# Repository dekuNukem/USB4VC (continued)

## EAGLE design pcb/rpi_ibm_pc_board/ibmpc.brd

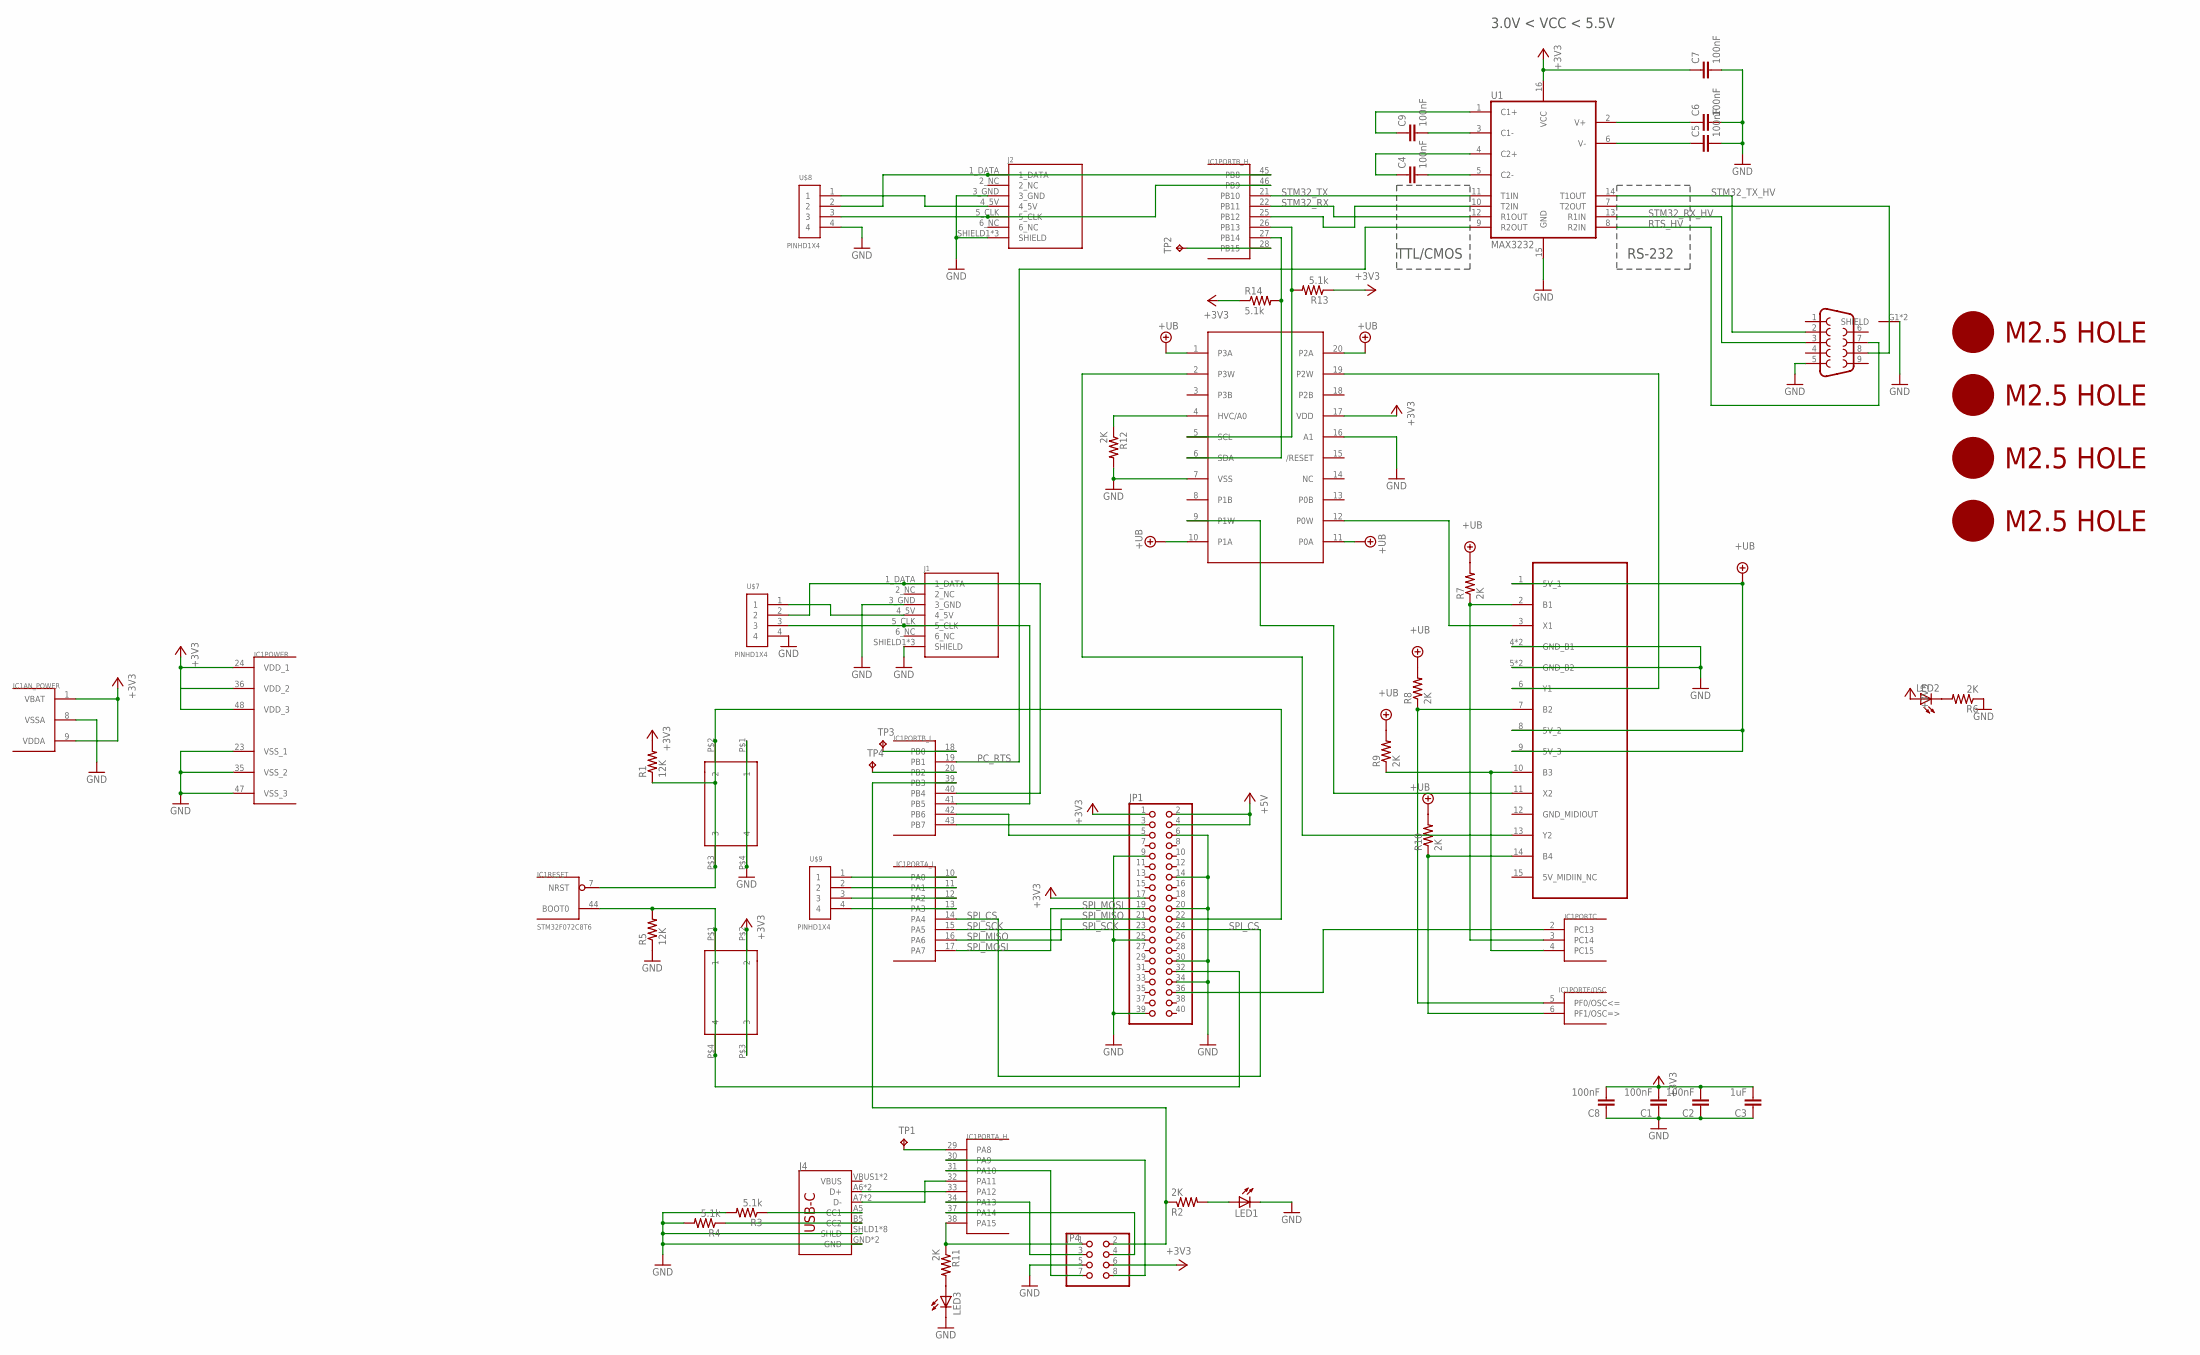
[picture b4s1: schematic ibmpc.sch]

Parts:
C1, C2, C4, C5, C6, C7, C8, C9: 100nF; 0805@1
C3: 1uF; 0805@1
IC1: STM32F072C8T6; TQFP48
J1, J2: DIN7
J3: DB9MALE; DB9_MALE
J4: USB_C16PIN; USB-C-16P
JP1: PINHD-2X20-BIG; 2X20-BIG
JP4: PINHD-2X4; 2X04
LED1, LED2, LED3: LEDCHIP-LED0805; CHIP-LED0805
R1, R5: 12K; 0805
R2, R6, R7, R8, R9, R10, R11, R12: 2K; 0805
R3, R4, R13, R14: 5.1k; 0805
SW1, SW4: 324_SW; 342_SWICH_FOOT
TP1, TP2, TP3, TP4: TPTP12R; TP12R
U1: MAX3232; SO016
U$1: GAMEPORT_15P; DA15
U$2, U$3, U$4, U$5: M2.5HOLE
U$6: MCP4451; TSSOP20
U$7, U$8, U$9: PINHD1X4; 1X04-CLEANBIG

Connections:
+3V3: C1.2, C2.2, C3.2, C7.1, C8.2, IC1.1 (VBAT), IC1.9 (VDDA), IC1.24 (VDD_1), IC1.36 (VDD_2), IC1.48 (VDD_3), JP1.1, JP1.17, JP4.6, LED2.A, R1.2, R13.1, R14.1, SW1.P$2 (2), SW1.P$3 (3), U1.16 (VCC), U$6.17 (VDD)
+5V: JP1.2, JP1.4
+UB: R7.2, R8.2, R9.2, R10.2, U$1.1 (5V_1), U$1.8 (5V_2), U$1.9 (5V_3), U$6.1 (P3A), U$6.10 (P1A), U$6.11 (P0A), U$6.20 (P2A)
C1+: C9.1, U1.1 (C1+)
C1-: C9.2, U1.3 (C1-)
C2+: C4.1, U1.4 (C2+)
C2-: C4.2, U1.5 (C2-)
GND: C1.1, C2.1, C3.1, C5.2, C6.2, C7.2, C8.1, IC1.8 (VSSA), IC1.23 (VSS_1), IC1.35 (VSS_2), IC1.47 (VSS_3), J1.3_GND, J1.SHIELD1 (SHIELD), J1.SHIELD2 (SHIELD), J1.SHIELD3 (SHIELD), J2.3_GND, J2.SHIELD1 (SHIELD), J2.SHIELD2 (SHIELD), J2.SHIELD3 (SHIELD), J3.5, J3.G1 (SHIELD), J3.G2 (SHIELD), J4.GND, J4.GND2 (GND), J4.SHLD1 (SHLD), J4.SHLD2 (SHLD), J4.SHLD3 (SHLD), J4.SHLD4 (SHLD), J4.SHLD5 (SHLD), J4.SHLD6 (SHLD), J4.SHLD7 (SHLD), J4.SHLD8 (SHLD), JP1.6, JP1.9, JP1.14, JP1.20, JP1.25, JP1.30, JP1.34, JP1.39, JP4.5, LED1.C, LED3.C, R3.2, R4.2, R5.1, R6.1, R12.2, SW4.P$1 (1), SW4.P$4 (4), U1.15 (GND), U$1.4 (GND_B1), U$1.5 (GND_B2), U$1.G1 (GND_B1), U$1.G2 (GND_B2), U$6.7 (VSS), U$6.16 (A1), U$7.4, U$8.4
unnamed: J4.A5 (CC1), R3.1
unnamed: LED1.A, R2.2
unnamed: J1.4_5V, U$7.1
unnamed: J2.4_5V, U$8.1
unnamed: IC1.41 (PB5), J1.5_CLK, U$7.3
unnamed: IC1.39 (PB3), JP4.2, R2.1
unnamed: J4.B5 (CC2), R4.1
unnamed: IC1.33 (PA12), J4.A6 (D+), J4.B6 (D+)
unnamed: IC1.32 (PA11), J4.A7 (D-), J4.B7 (D-)
unnamed: IC1.45 (PB8), J2.1_DATA, U$8.2
unnamed: IC1.46 (PB9), J2.5_CLK, U$8.3
unnamed: IC1.31 (PA10), JP4.7
unnamed: IC1.7 (NRST), JP1.22, R1.1, SW4.P$2 (2), SW4.P$3 (3)
unnamed: IC1.30 (PA9), JP4.8
unnamed: IC1.34 (PA13), JP4.3
unnamed: IC1.37 (PA14), JP4.4
unnamed: IC1.3 (PC14), R7.1, U$1.2 (B1)
unnamed: IC1.44 (BOOT0), JP1.32, R5.2, SW1.P$1 (1), SW1.P$4 (4)
unnamed: IC1.5 (PF0/OSC<=), R8.1, U$1.7 (B2)
unnamed: IC1.4 (PC15), R9.1, U$1.10 (B3)
unnamed: IC1.6 (PF1/OSC=>), R10.1, U$1.14 (B4)
unnamed: IC1.42 (PB6), JP1.5
unnamed: IC1.43 (PB7), JP1.3
unnamed: IC1.25 (PB12), U1.10 (T2IN)
unnamed: J3.8, U1.7 (T2OUT)
unnamed: IC1.40 (PB4), J1.1_DATA, U$7.2
unnamed: IC1.38 (PA15), JP4.1, R11.1
unnamed: LED3.A, R11.2
unnamed: LED2.C, R6.2
unnamed: IC1.27 (PB14), R14.2, U$6.6 (SDA)
unnamed: IC1.26 (PB13), R13.2, U$6.5 (SCL)
unnamed: R12.1, U$6.4 (HVC/A0)
unnamed: U$1.3 (X1), U$6.12 (P0W)
unnamed: U$1.11 (X2), U$6.9 (P1W)
unnamed: U$1.6 (Y1), U$6.19 (P2W)
unnamed: U$1.13 (Y2), U$6.2 (P3W)
unnamed: IC1.2 (PC13), JP1.36
unnamed: IC1.10 (PA0), U$9.1
unnamed: IC1.11 (PA1), U$9.2
unnamed: IC1.12 (PA2), U$9.3
unnamed: IC1.13 (PA3), U$9.4
unnamed: IC1.29 (PA8), TP1.TP
unnamed: IC1.28 (PB15), TP2.TP
unnamed: IC1.20 (PB2), TP4.TP
unnamed: IC1.18 (PB0), TP3.TP
PC_RTS: IC1.19 (PB1), U1.9 (R2OUT)
RTS_HV: J3.7, U1.8 (R2IN)
SPI_CS: IC1.14 (PA4), JP1.24
SPI_MISO: IC1.16 (PA6), JP1.21
SPI_MOSI: IC1.17 (PA7), JP1.19
SPI_SCK: IC1.15 (PA5), JP1.23
STM32_RX: IC1.22 (PB11), U1.12 (R1OUT)
STM32_RX_HV: J3.3, U1.13 (R1IN)
STM32_TX: IC1.21 (PB10), U1.11 (T1IN)
STM32_TX_HV: J3.2, U1.14 (T1OUT)
V+: C6.1, U1.2 (V+)
V-: C5.1, U1.6 (V-)

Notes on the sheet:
RS-232
TTL/CMOS
3.0V < VCC < 5.5V

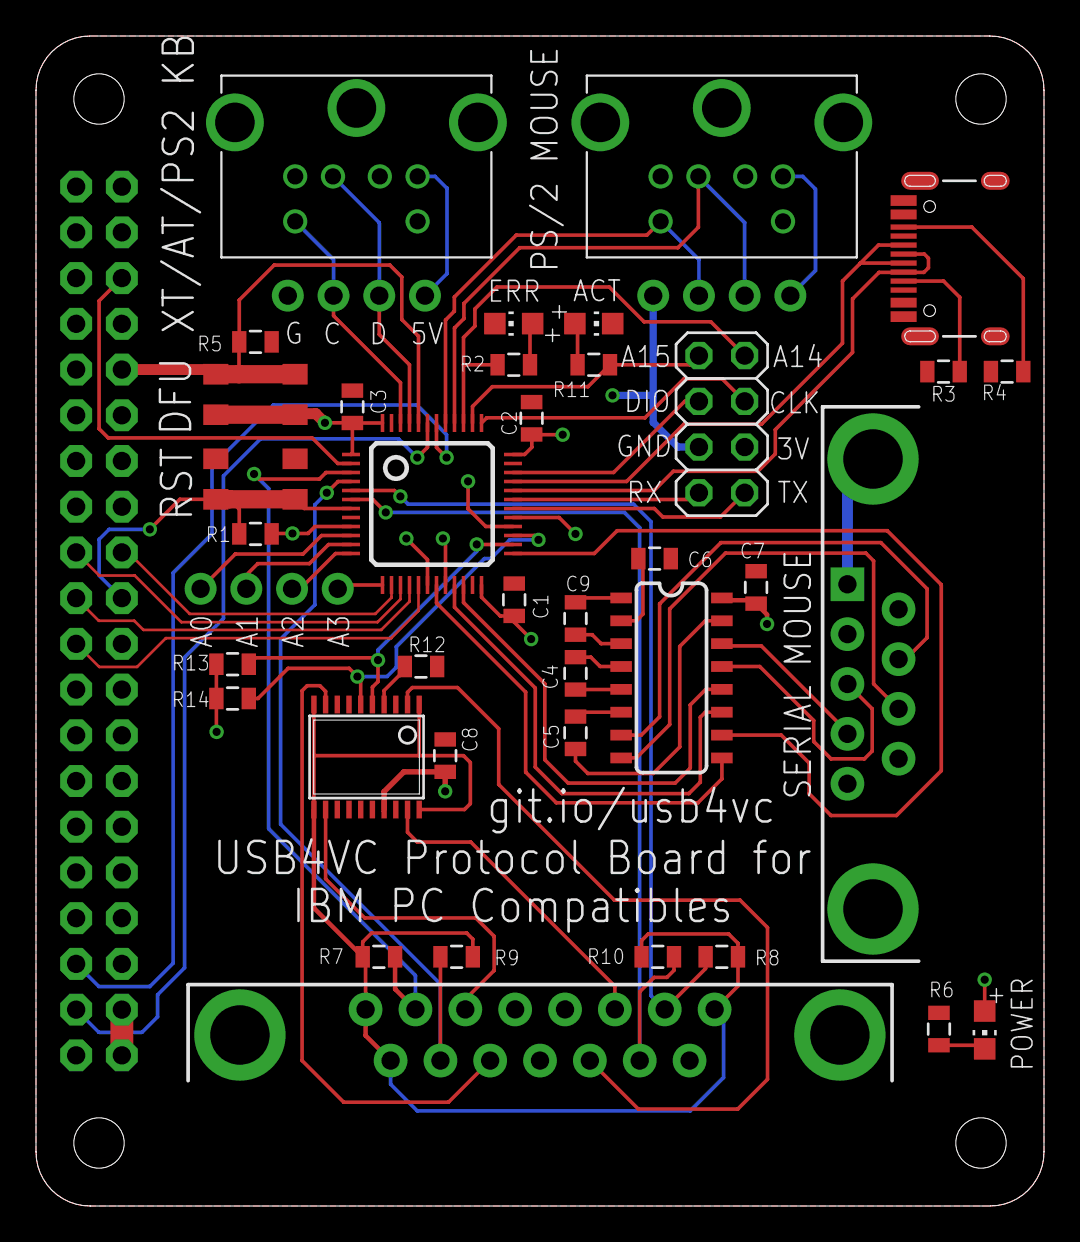
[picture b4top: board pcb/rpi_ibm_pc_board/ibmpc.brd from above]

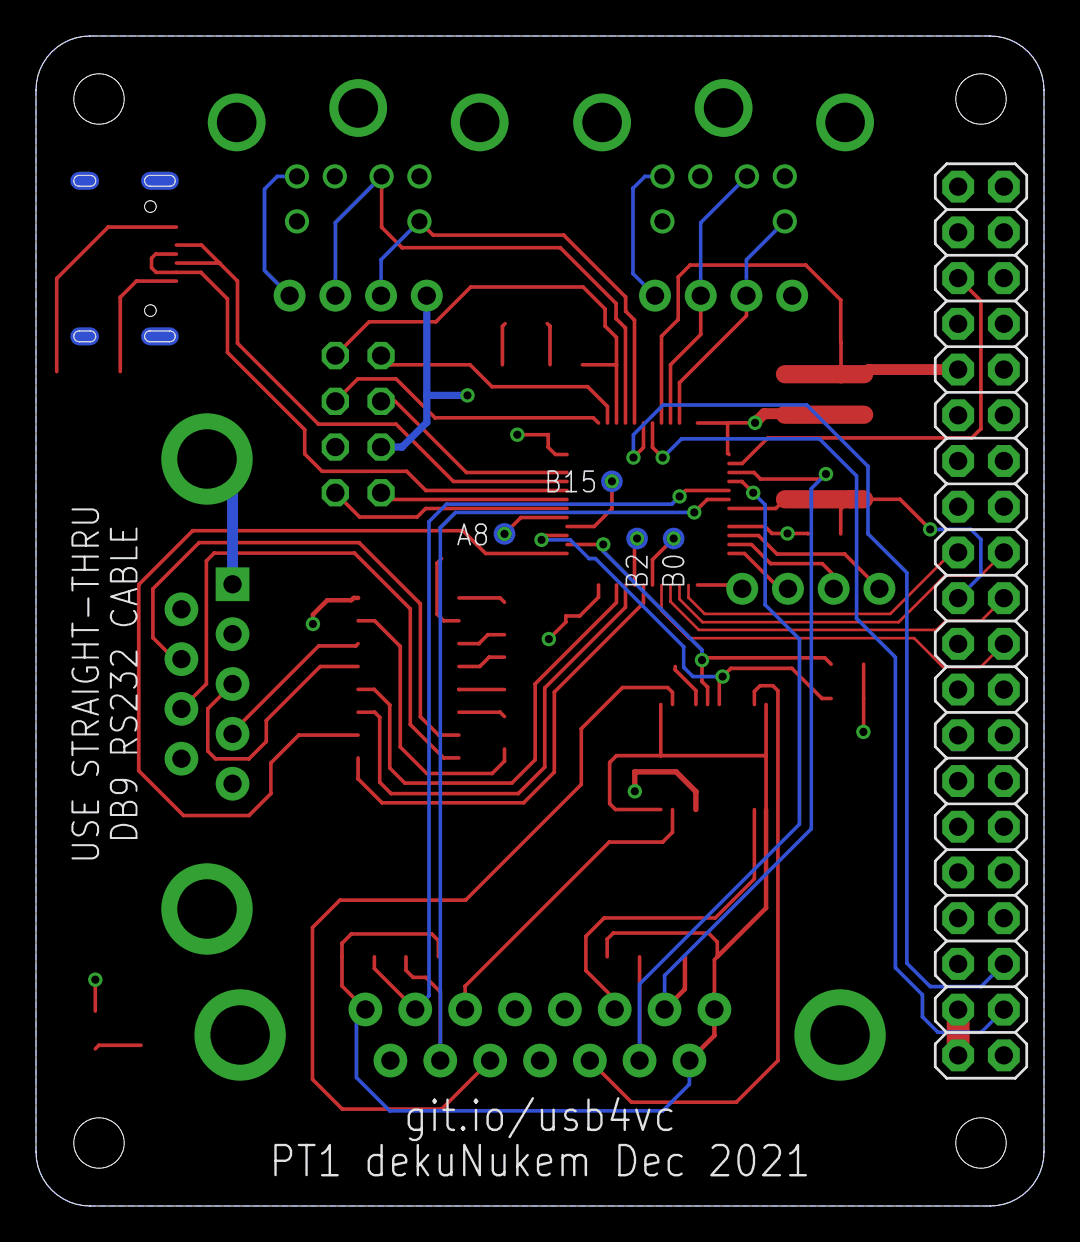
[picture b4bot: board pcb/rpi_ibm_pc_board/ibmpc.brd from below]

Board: 2 copper layers, 56.0 x 65.0 mm, 49 parts (5 on the bottom side), 65 nets.

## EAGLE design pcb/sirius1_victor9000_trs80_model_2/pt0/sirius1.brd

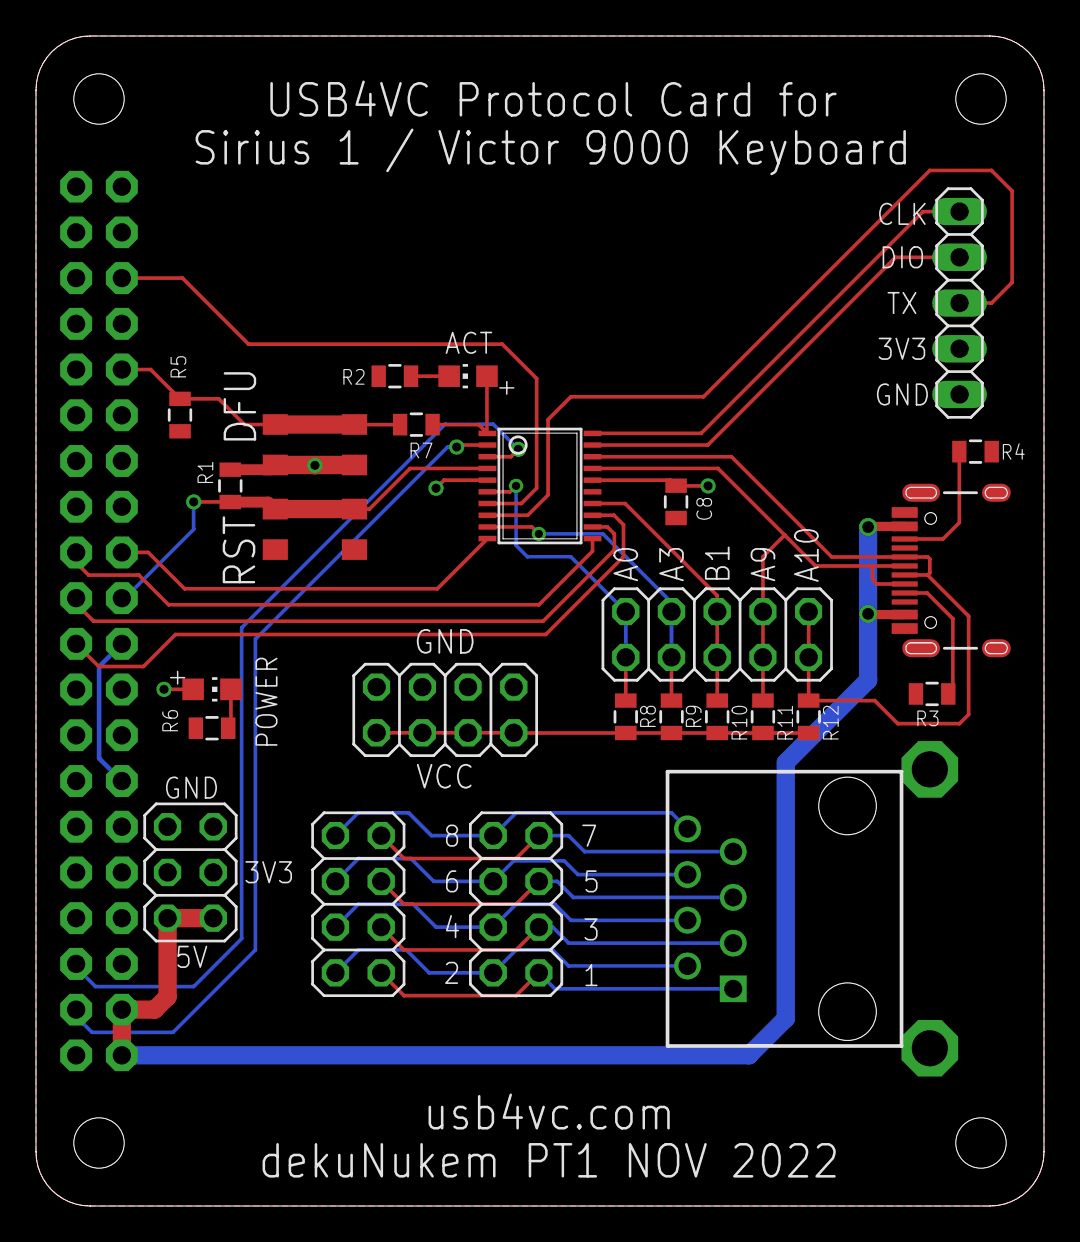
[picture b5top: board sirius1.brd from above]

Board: 2 copper layers, 56.0 x 65.0 mm, 33 parts (1 on the bottom side), 34 nets.

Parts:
C8: 100nF; 0805@1
IC3: STM32F042F4; TSSOP20
J4: USB-C-16P
JP1: 2X20-BIG
JP2, JP3, JP6: 2X04
JP4: 2X03
JP5: 1X05
JP8: 2X05
LED1, LED2: CHIP-LED0805
R1, R3, R4, R5, R8, R9, R10, R11, R12: 5.1K; 0805
R2, R6, R7: 2K; 0805
SW1, SW4: 324_SW; 342_SWICH_FOOT
TP1, TP2: TPSQPAD1-20; P1-20
U1: RJ45; RJ45-8
U$2, U$3, U$4, U$5: M2.5HOLE

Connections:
+3V3: C8.2, IC3.5, IC3.16, JP1.1, JP1.17, JP4.3, JP4.4, JP5.4, LED2.A, R1.2, SW1.P$2, SW1.P$3
+5V: J4.VBUS1, J4.VBUS2, JP1.2, JP1.4, JP4.1, JP4.2
GND: C8.1, IC3.15, J4.GND, J4.GND2, J4.SHLD1, J4.SHLD2, J4.SHLD3, J4.SHLD4, J4.SHLD5, J4.SHLD6, J4.SHLD7, J4.SHLD8, JP1.6, JP1.9, JP1.14, JP1.20, JP1.25, JP1.30, JP1.34, JP1.39, JP2.2, JP2.4, JP2.6, JP2.8, JP4.5, JP4.6, JP5.5, R2.1, R3.2, R4.2, R5.1, R6.1, SW4.P$1, SW4.P$4, TP1.TP, TP2.TP
unnamed: J4.A5, R3.1
unnamed: JP1.32, R5.2, R7.1, SW1.P$1, SW1.P$4
unnamed: IC3.17, J4.A7, J4.B7, JP8.7, JP8.8, R11.1
unnamed: IC3.8, JP5.3
unnamed: IC3.19, JP5.2
unnamed: J4.B5, R4.1
unnamed: IC3.20, JP5.1
unnamed: IC3.1, LED1.A, R7.2
unnamed: IC3.2, JP1.3
unnamed: IC3.3, JP1.5
unnamed: IC3.7, JP1.36
unnamed: IC3.4, JP1.22, R1.1, SW4.P$2, SW4.P$3
unnamed: JP3.1, JP6.1, U1.1
unnamed: JP3.2, JP6.2, U1.2
unnamed: JP3.3, JP6.3, U1.3
unnamed: LED1.C, R2.2
unnamed: JP3.4, JP6.4, U1.4
unnamed: JP3.5, JP6.5, U1.5
unnamed: JP3.6, JP6.6, U1.6
unnamed: JP3.7, JP6.7, U1.7
unnamed: JP3.8, JP6.8, U1.8
unnamed: IC3.9, JP8.3, JP8.4, R9.1
unnamed: IC3.14, JP8.5, JP8.6, R10.1
unnamed: IC3.18, J4.A6, J4.B6, JP8.9, JP8.10, R12.1
unnamed: JP2.1, JP2.3, JP2.5, JP2.7, R8.2, R9.2, R10.2, R11.2, R12.2
unnamed: LED2.C, R6.2
unnamed: IC3.6, JP8.1, JP8.2, R8.1
SPI_CS: IC3.10, JP1.24
SPI_MISO: IC3.12, JP1.21
SPI_MOSI: IC3.13, JP1.19
SPI_SCK: IC3.11, JP1.23
